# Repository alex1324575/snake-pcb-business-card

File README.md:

# Snake PCB Business Card

A USB-powered PCB business card with a 10 × 9 LED matrix, five buttons and Snake firmware. A passive NFC tag and a silkscreen QR code carry the contact URL.

**Firmware simulation.** The board and enlarged display show the same 90 PWM values from the C firmware: start, turn, collect four food pixels, hit a wall and display the score. See the [gameplay demo](docs/revc/GAMEPLAY_DEMO.md) for source, capture and reproduction details. This is a host simulation; hardware execution remains untested.

| Rev C — Top | Rev C — Bottom |
|---|---|
|  |  |

3D assembly previews use the current Rev C layout and all 125 fitted parts. The separate [rotation preview](docs/images/revc-3d-rotation.gif) shows assembly geometry with unlit LEDs. A [static isometric view](docs/images/revc-3d-isometric.png) and [model provenance](docs/revc/3D_VISUALIZATION.md) are also available. Public artwork uses **ALEX XU** and **https://example.com/**.

## Current revision

**Rev C is the current Altium prototype design.** CAD corrections, native validation and final CAM review are complete. Supplier process acceptance and first-article qualification remain open; all 14 physical tests are **NOT TESTED**.

| Check | Recorded result — 28 October 2026 |
|---|---|
| Native PCB DRC | 0 violations, 0 warnings, 0 waivers; all 43 stored rule records unchanged |
| Native schematic validation | 0 errors, 2 reviewed reset-bias warnings, retained without suppression |
| Saved-source audit | 135 schematic instances, 29 symbols, 15 footprints; 217 firmware contract checks passed |
| Manufacturing output review | Nine Gerbers and two plated-hole/slot NC files matched to the final saved PCB |
| Hardware qualification | P01–P14 NOT TESTED; no assembled-board result recorded |

The [verification guide](docs/VERIFICATION.md) identifies the reports, public-copy transformations and test limits. Layout compromises, including retained orthogonal NFC coil corners, are listed in [layout tradeoffs](docs/revc/LAYOUT_TRADEOFFS.md).

## Hardware

| Feature | Rev C implementation |
|---|---|
| Board | 85.6 × 54 mm, two layers, nominal 0.8 mm, four R2 corners |
| Finish | Black solder mask, white silkscreen, ENIG |
| MCU | STM32G030K8T6, Cortex-M0+, 64 KB Flash / 8 KB SRAM |
| Display | 90 red LEDs and IS31FL3737B PWM driver |
| Input | Four direction buttons and START |
| Power | USB-C 5 V, TPS7A2433DBVR 3.3 V regulator; no battery |
| Contact | Bottom QR artwork and ST25TN01K passive NFC tag |
| Programming | SWD test pads on both faces; TP7/SWCLK is on Top |

USB-C supplies power only. Firmware is programmed over SWD. NFC operates independently of USB power and is provisioned separately from the MCU.

## Open the design

Open [SnakeCard_RevC.PrjPcb](altium/SnakeCard_RevC.PrjPcb) in Altium Designer. The project contains the single-sheet schematic, routed PCB and local schematic/footprint libraries. The [Altium guide](docs/ALTIUM.md) describes the files and validation procedure.

| Purpose | Current Rev C files |
|---|---|
| Review the circuit | [Native schematic PDF](exports/SnakeCard_RevC_Schematic.pdf) and [hardware notes](docs/HARDWARE.md) |
| Review checks | [Verification](docs/VERIFICATION.md) and [final status record](verification/revc/FINAL_CHECK_STATUS.json) |
| Select parts | [Controlled BOM — SC-REVC-LCSC-P1](docs/revc/assembly/BOM.md) |
| Fabricate | [Gerber/NC files](fabrication/revc/) and [fabrication specification](docs/revc/FABRICATION_NOTES.md) |
| Assemble | [Assembly guide](docs/ASSEMBLY.md), [placement register](docs/revc/assembly/PLACEMENT_REGISTER.md) and [drawings](docs/revc/assembly/ASSEMBLY_REFERENCE.html) |
| Test the first board | [Bring-up](docs/BRINGUP.md) and [P01–P14 qualification record](docs/revc/electrical/QUALIFICATION_PLAN.md) |

The root KiCad project and earlier exports remain as the **historical KiCad revision**. They were not updated to Rev C. Do not combine their BOM, footprint, stencil, SWD or fabrication data with Rev C. See [revision history](docs/REVISION_HISTORY.md).

## Firmware

The C11 firmware uses register-level board support, with no heap or RTOS. It implements Snake, button debounce, PWM display control and fault recovery. Rev C retains the tested firmware source and release images; the original `RevB` binary filenames are retained. The native Rev C pin contract was checked separately. MCU execution remains untested.

From the repository root, with Python 3.9+ and an Arm GNU toolchain installed:

```sh
python firmware/tools/build.py --build
```

Host tests also require GCC, Clang or Microsoft C++ Build Tools:

```sh
python firmware/tools/build.py --test-host --sanitize
```

The [firmware guide](firmware/README.md) covers toolchains, checksums and controls. `firmware/tools/check_board_contract.py` checks the historical KiCad inputs; it does not replace the saved-native Rev C audit.

### Controls

- Press START to begin, pause or resume.
- Use the direction buttons to steer toward the flashing food pixel.
- Hold START for about 0.8 seconds to return to idle.
- Hold UP while idle to view the highest score from the current power session.
- Hold START during power-up to enter the LED/button diagnostic; release it and press START again to exit.

Assemble and measure one controlled first article before building additional cards. Use the [prototype plan](docs/PROTOTYPE_PLAN.md) to track supplier, assembly and qualification gates. Contribution and license information are in [CONTRIBUTING](CONTRIBUTING.md) and [THIRD_PARTY_NOTICES](THIRD_PARTY_NOTICES.md).

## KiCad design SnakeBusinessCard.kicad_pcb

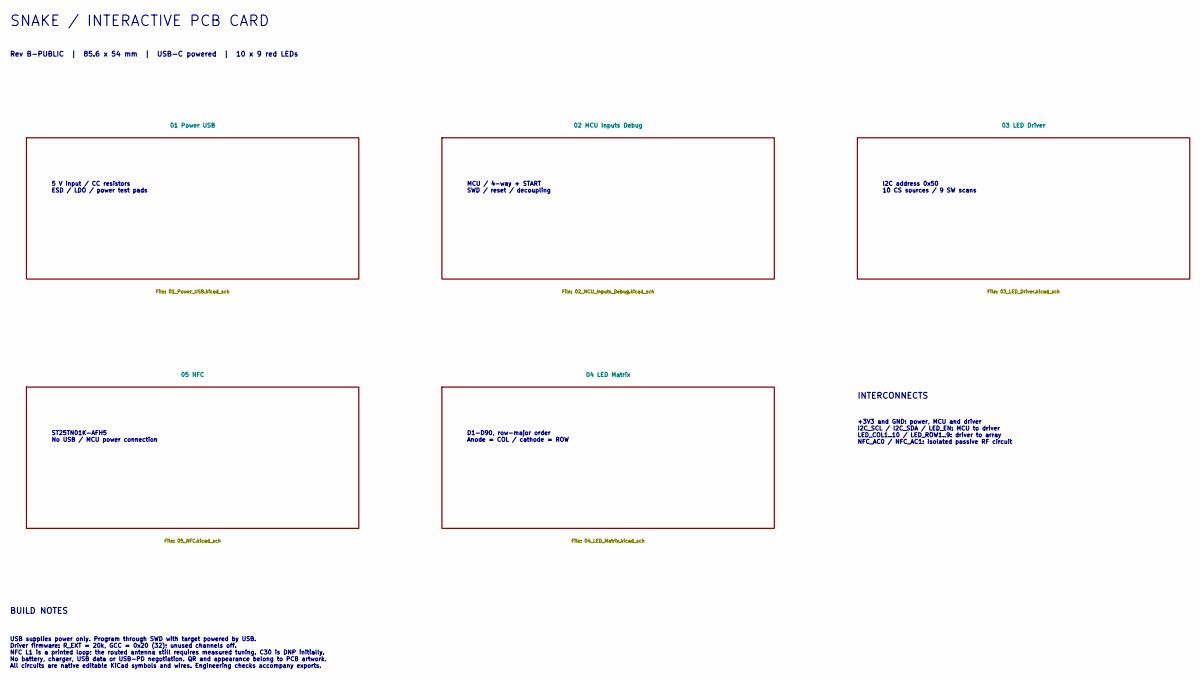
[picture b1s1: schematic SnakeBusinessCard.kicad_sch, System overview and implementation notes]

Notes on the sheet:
SNAKE / INTERACTIVE PCB CARD
Rev B-PUBLIC | 85.6 x 54 mm | USB-C powered | 10 x 9 red LEDs
5 V input / CC resistors ESD / LDO / power test pads
MCU / 4-way + START SWD / reset / decoupling
I2C address 0x50 10 CS sources / 9 SW scans
D1-D90, row-major order Anode = COL / cathode = ROW
ST25TN01K-AFH5 No USB / MCU power connection
INTERCONNECTS
+3V3 and GND: power, MCU and driver I2C_SCL / I2C_SDA / LED_EN: MCU to driver LED_COL1..10 / LED_ROW1..9: driver to array NFC_AC0 / NFC_AC1: isolated passive RF circuit
BUILD NOTES
USB supplies power only. Program through SWD with target powered by USB. Driver firmware: R_EXT = 20k, GCC = 0x20 (32); unused channels off. NFC L1 is a printed loop; the routed antenna still requires measured tuning. C30 is DNP initially. No battery, charger, USB data or USB-PD negotiation. QR and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

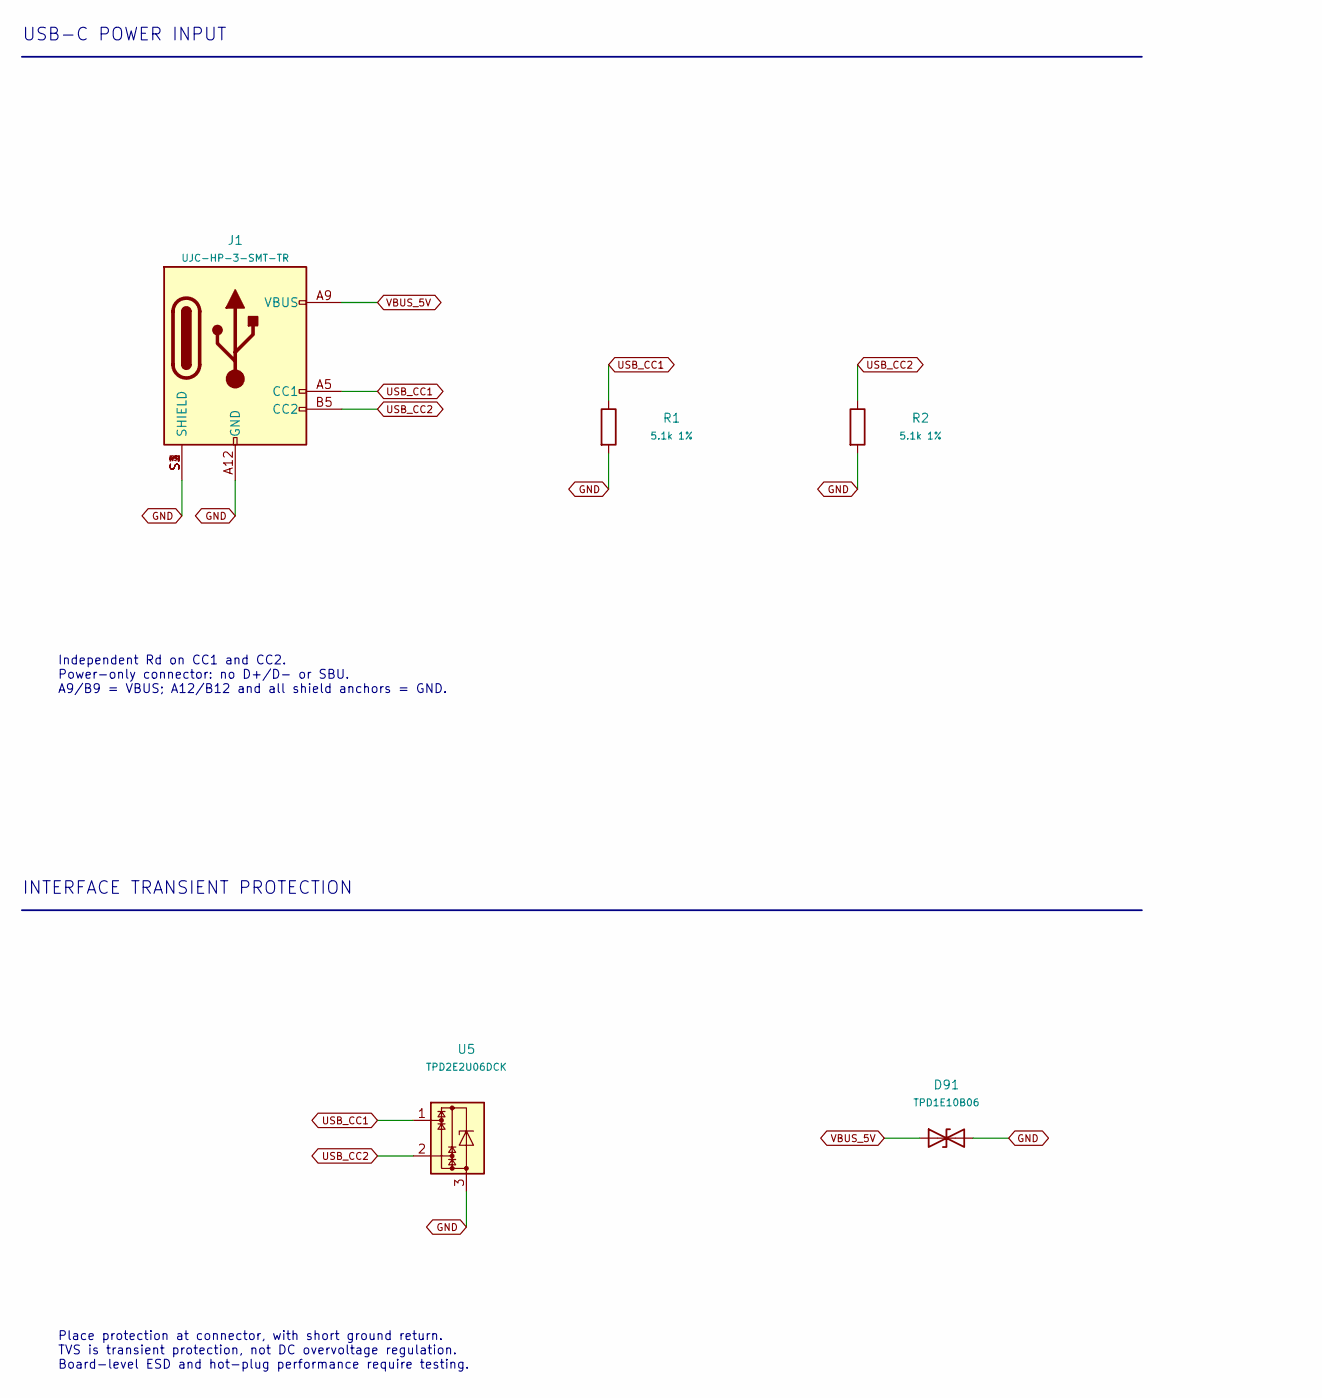
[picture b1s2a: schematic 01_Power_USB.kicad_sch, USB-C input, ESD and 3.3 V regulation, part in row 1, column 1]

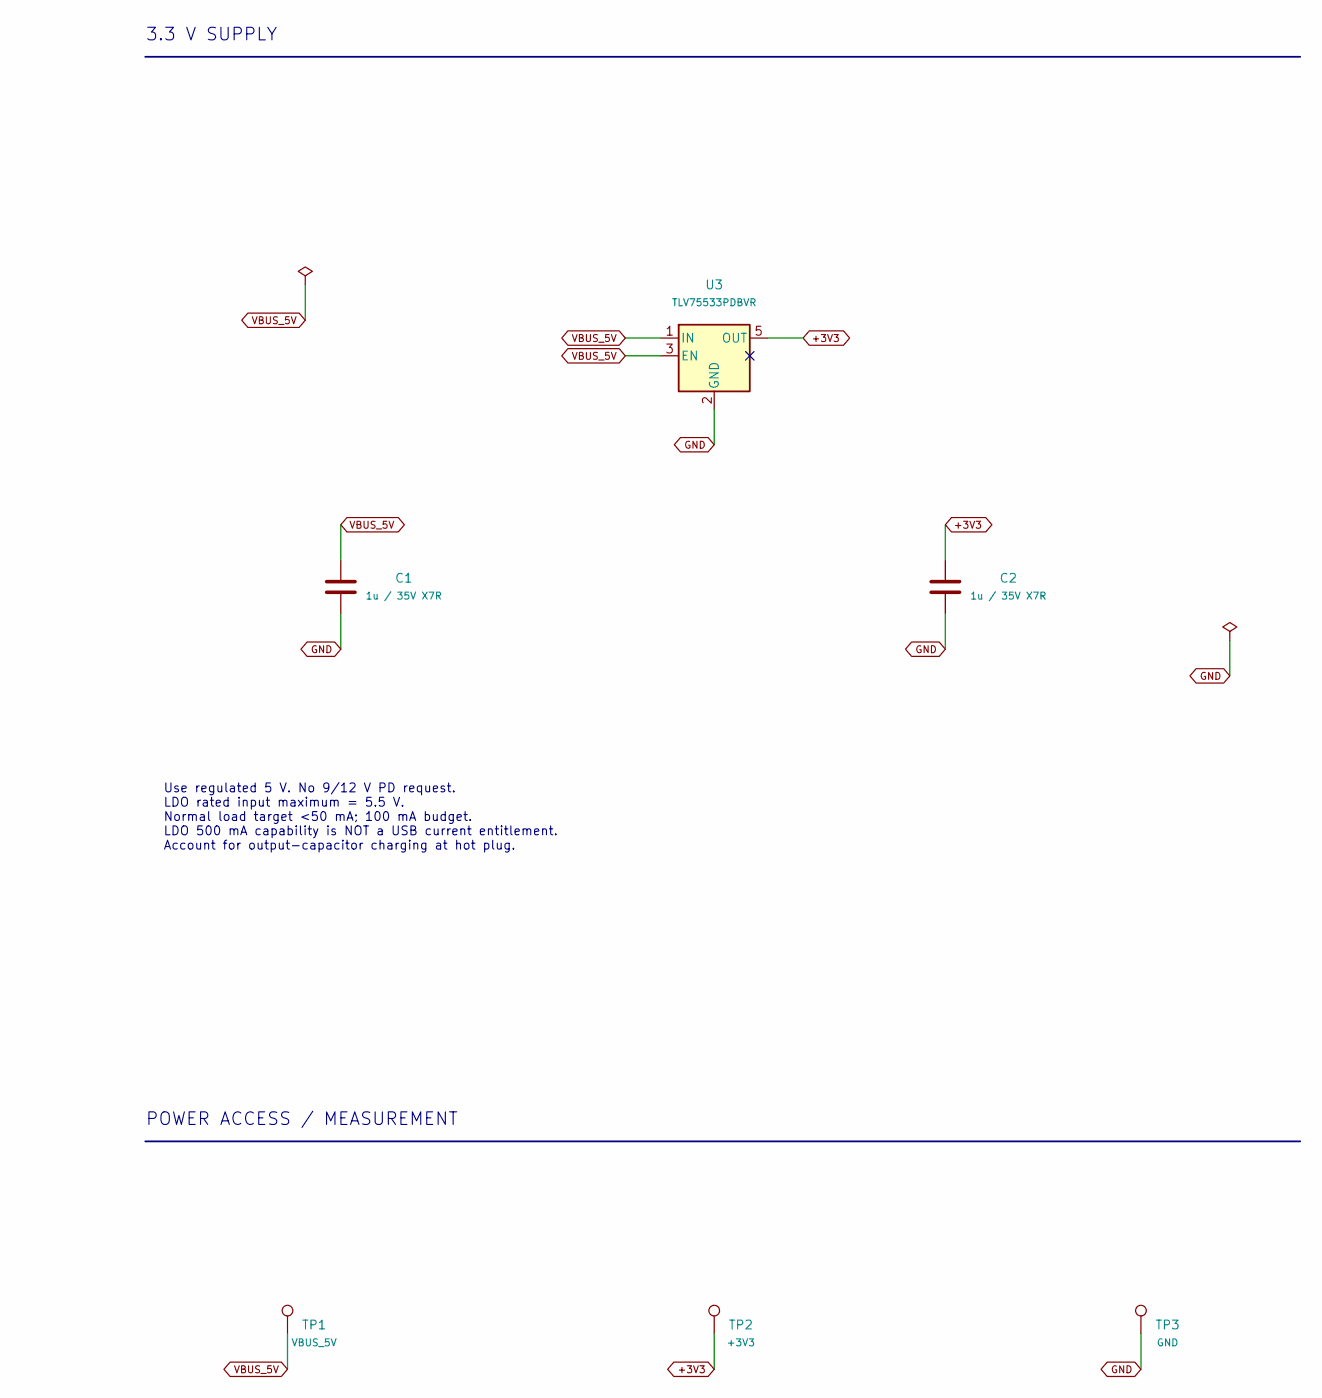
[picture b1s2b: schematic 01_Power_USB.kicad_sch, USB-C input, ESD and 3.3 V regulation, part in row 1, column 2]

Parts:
C1, C2: 1u / 35V X7R; C_0603_1608Metric; MPN C1608X7R1V105K080AC
D91: TPD1E10B06; D_SOD-523; MPN TPD1E10B06DYAR
J1: UJC-HP-3-SMT-TR; CUI_UJC-HP-3-SMT-TR; MPN UJC-HP-3-SMT-TR
R1, R2: 5.1k 1%; R_0603_1608Metric; MPN ERJ3EKF5101V
TP1: VBUS_5V; TestPoint_Pad_D1.0mm
TP2: +3V3; TestPoint_Pad_D1.0mm
TP3: GND; TestPoint_Pad_D1.0mm
U3: TLV75533PDBVR; SOT-23-5; MPN TLV75533PDBVR
U5: TPD2E2U06DCK; SOT-323_SC-70; MPN TPD2E2U06DCKR

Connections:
+3V3: C2.1, TP2.1, U3.5 (OUT); also elsewhere on the board
GND: C1.2, C2.2, D91.2 (A2), J1.A12 (GND), J1.B12 (GND), J1.S1 (SHIELD), J1.S2 (SHIELD), J1.S3 (SHIELD), J1.S4 (SHIELD), R1.2, R2.2, TP3.1, U3.2 (GND), U5.3; also elsewhere on the board
USB_CC1: J1.A5 (CC1), R1.1, U5.1
USB_CC2: J1.B5 (CC2), R2.1, U5.2
VBUS_5V: C1.1, D91.1 (A1), J1.A9 (VBUS), J1.B9 (VBUS), TP1.1, U3.1 (IN), U3.3 (EN)

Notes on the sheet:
USB-C POWER INPUT
Independent Rd on CC1 and CC2. Power-only connector: no D+/D- or SBU. A9/B9 = VBUS; A12/B12 and all shield anchors = GND.
INTERFACE TRANSIENT PROTECTION
Place protection at connector, with short ground return. TVS is transient protection, not DC overvoltage regulation. Board-level ESD and hot-plug performance require testing.
3.3 V SUPPLY
Use regulated 5 V. No 9/12 V PD request. LDO rated input maximum = 5.5 V. Normal load target <50 mA; 100 mA budget. LDO 500 mA capability is NOT a USB current entitlement. Account for output-capacitor charging at hot plug.
POWER ACCESS / MEASUREMENT

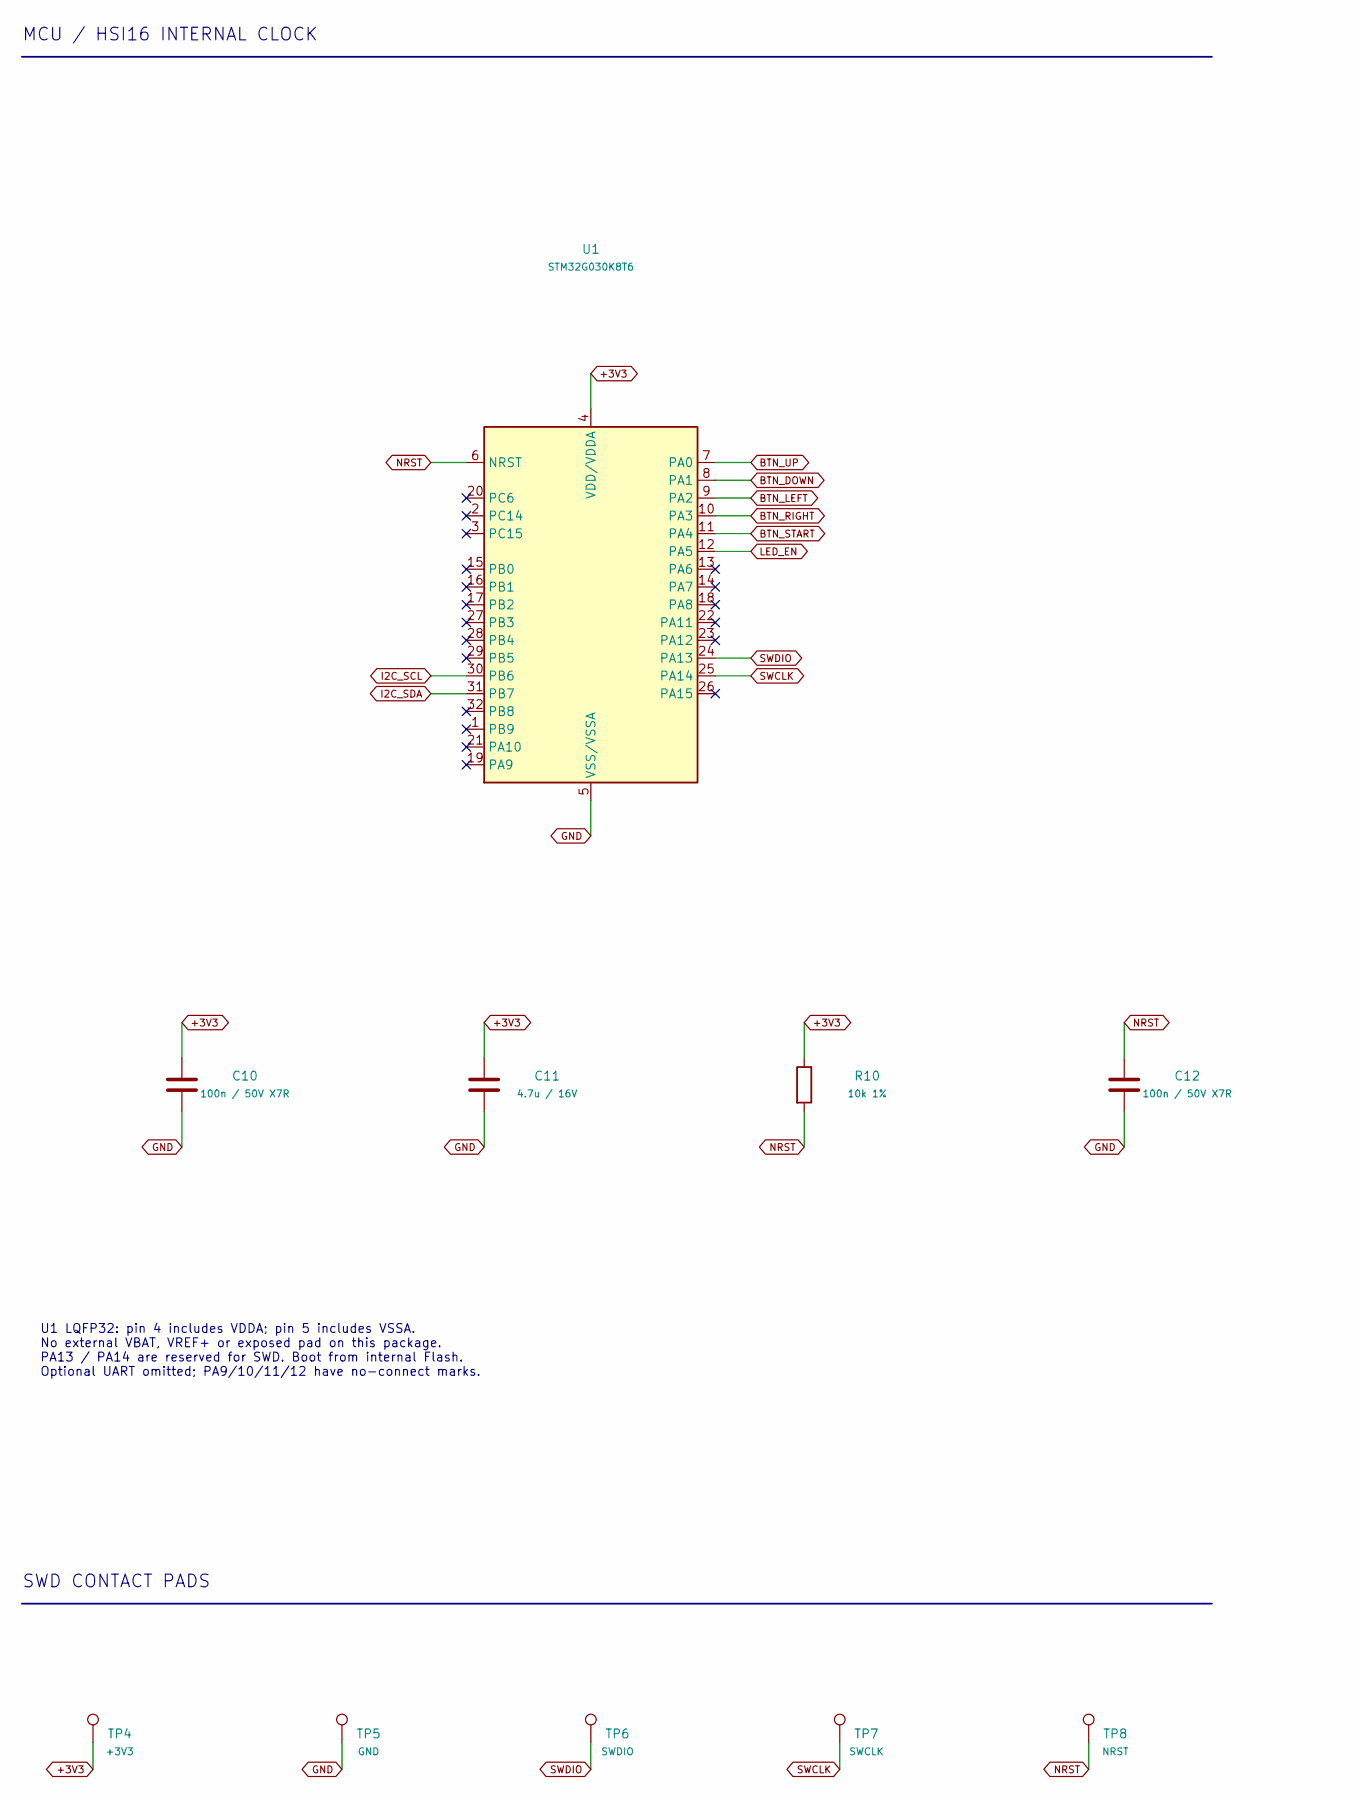
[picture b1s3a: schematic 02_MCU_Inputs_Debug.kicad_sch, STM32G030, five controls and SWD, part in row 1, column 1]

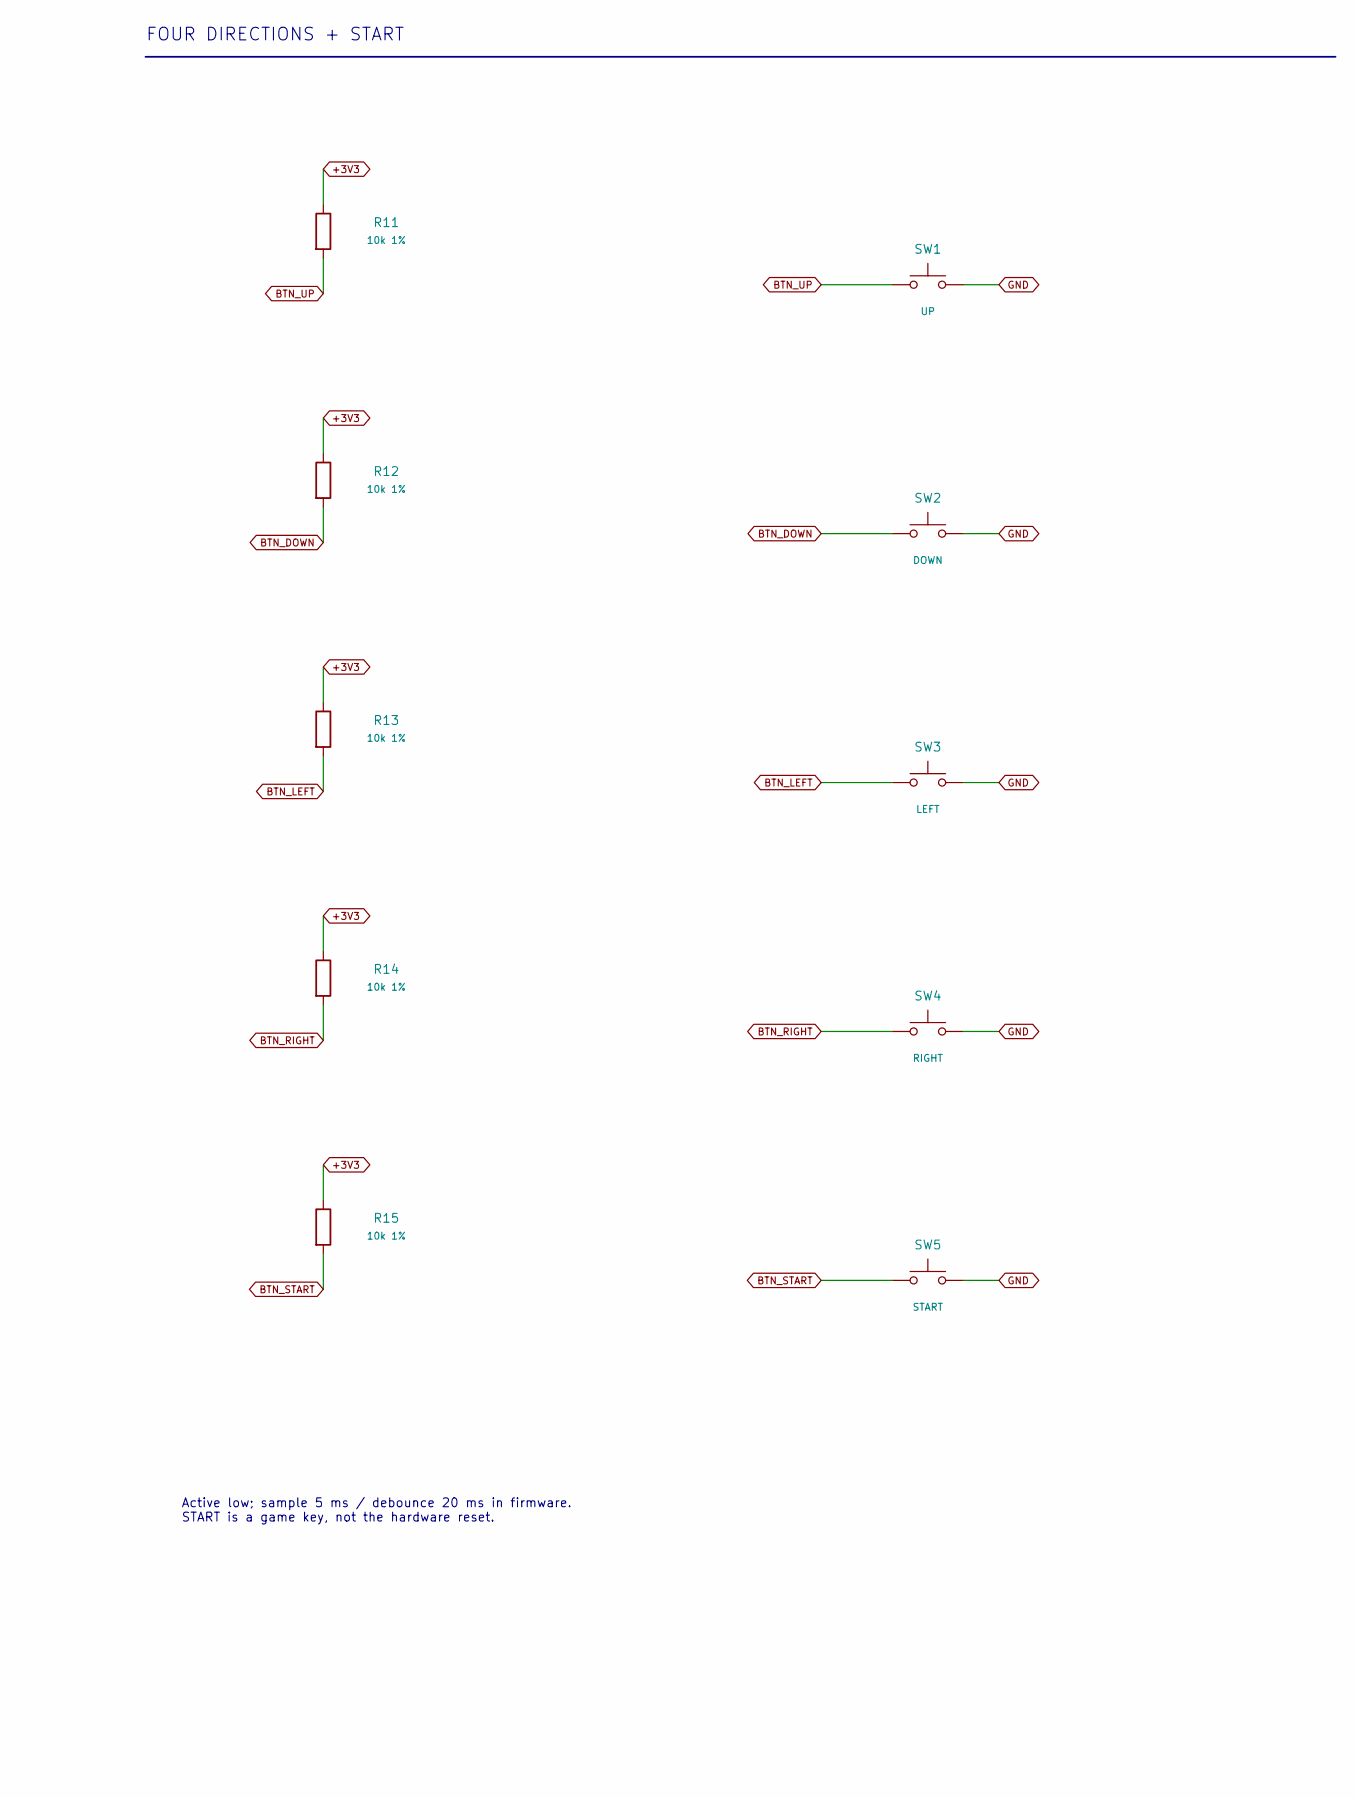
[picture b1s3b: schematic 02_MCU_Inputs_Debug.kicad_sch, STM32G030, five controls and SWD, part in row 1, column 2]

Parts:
C10, C12: 100n / 50V X7R; C_0603_1608Metric; MPN C1608X7R1H104K080AA
C11: 4.7u / 16V; C_0603_1608Metric; MPN GRM188Z71C475KE21D
R10, R11, R12, R13, R14, R15: 10k 1%; R_0603_1608Metric; MPN ERJ3EKF1002V
SW1: UP; SW_SPST_SKQG_WithStem; MPN SKQGABE010
SW2: DOWN; SW_SPST_SKQG_WithStem; MPN SKQGABE010
SW3: LEFT; SW_SPST_SKQG_WithStem; MPN SKQGABE010
SW4: RIGHT; SW_SPST_SKQG_WithStem; MPN SKQGABE010
SW5: START; SW_SPST_SKQG_WithStem; MPN SKQGABE010
TP4: +3V3; TestPoint_Pad_D1.0mm
TP5: GND; TestPoint_Pad_D1.0mm
TP6: SWDIO; TestPoint_Pad_D1.0mm
TP7: SWCLK; TestPoint_Pad_D1.0mm
TP8: NRST; TestPoint_Pad_D1.0mm
U1: STM32G030K8T6; LQFP-32_7x7mm_P0.8mm; MPN STM32G030K8T6

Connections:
+3V3: C10.1, C11.1, R10.1, R11.1, R12.1, R13.1, R14.1, R15.1, TP4.1, U1.4 (VDD/VDDA); also elsewhere on the board
BTN_DOWN: R12.2, SW2.1, U1.8 (PA1)
BTN_LEFT: R13.2, SW3.1, U1.9 (PA2)
BTN_RIGHT: R14.2, SW4.1, U1.10 (PA3)
BTN_START: R15.2, SW5.1, U1.11 (PA4)
BTN_UP: R11.2, SW1.1, U1.7 (PA0)
GND: C10.2, C11.2, C12.2, SW1.2, SW2.2, SW3.2, SW4.2, SW5.2, TP5.1, U1.5 (VSS/VSSA); also elsewhere on the board
I2C_SCL: U1.30 (PB6); also elsewhere on the board
I2C_SDA: U1.31 (PB7); also elsewhere on the board
LED_EN: U1.12 (PA5); also elsewhere on the board
NRST: C12.1, R10.2, TP8.1, U1.6 (NRST)
SWCLK: TP7.1, U1.25 (PA14)
SWDIO: TP6.1, U1.24 (PA13)

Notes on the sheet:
MCU / HSI16 INTERNAL CLOCK
U1 LQFP32: pin 4 includes VDDA; pin 5 includes VSSA. No external VBAT, VREF+ or exposed pad on this package. PA13 / PA14 are reserved for SWD. Boot from internal Flash. Optional UART omitted; PA9/10/11/12 have no-connect marks.
FOUR DIRECTIONS + START
Active low; sample 5 ms / debounce 20 ms in firmware. START is a game key, not the hardware reset.
SWD CONTACT PADS

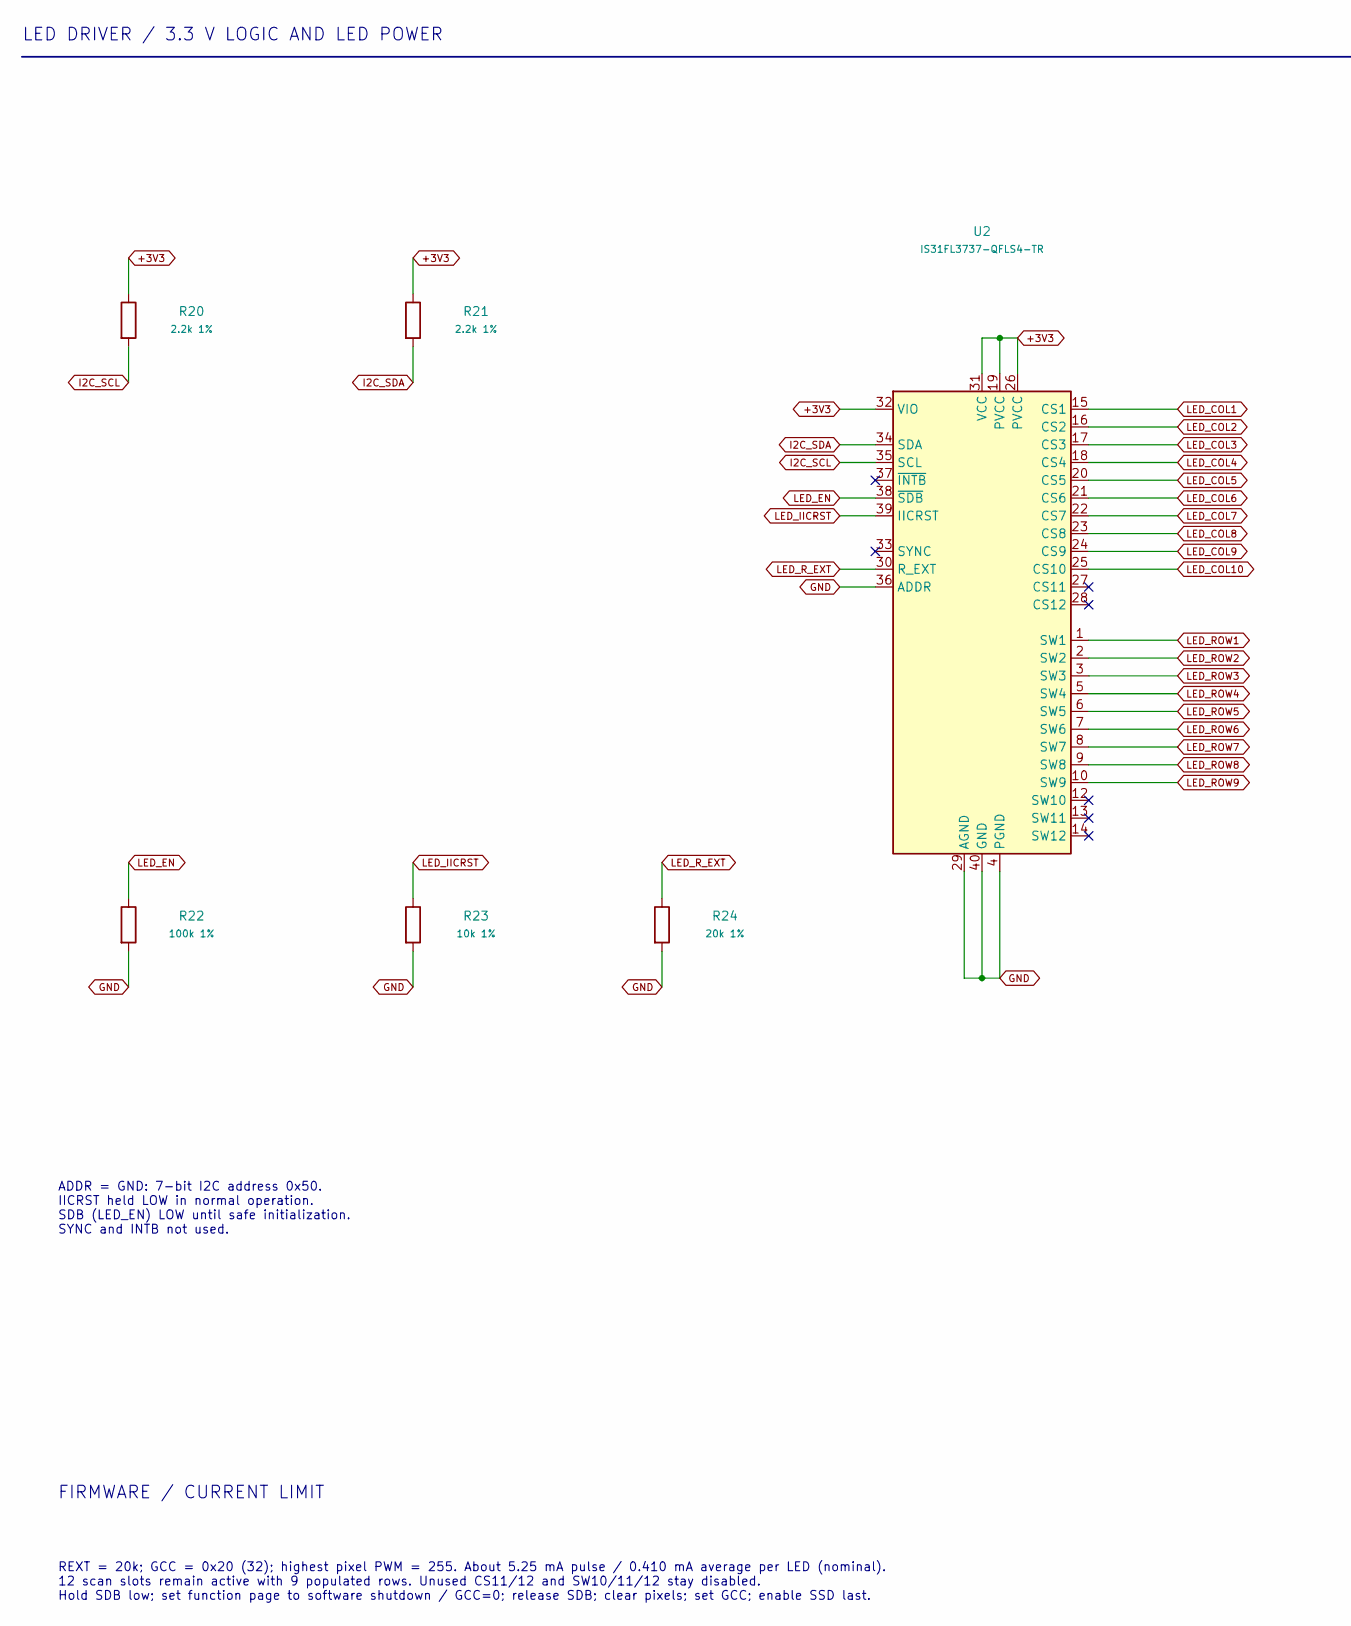
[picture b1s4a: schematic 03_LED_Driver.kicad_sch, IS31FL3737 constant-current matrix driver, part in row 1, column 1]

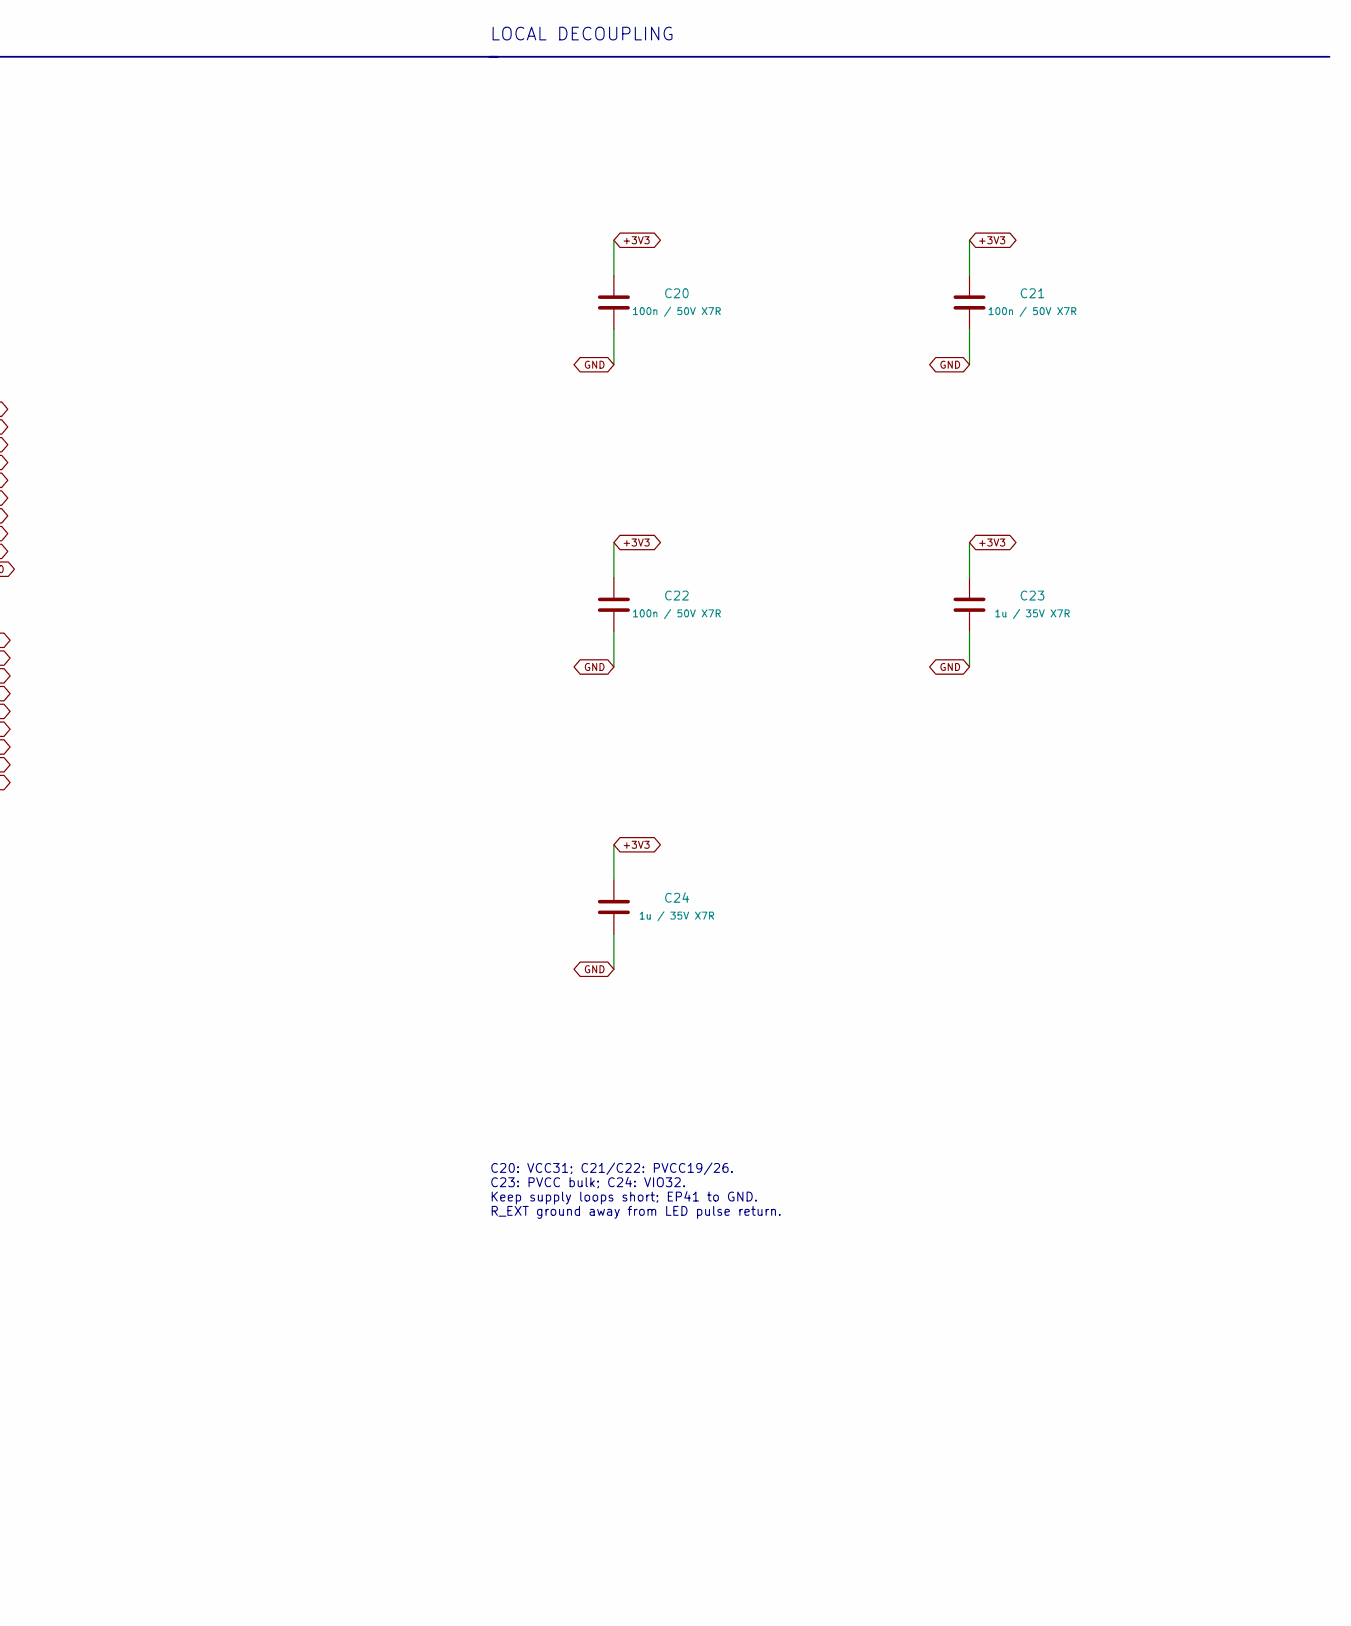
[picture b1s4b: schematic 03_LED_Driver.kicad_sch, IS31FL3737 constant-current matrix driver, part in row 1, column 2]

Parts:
C20, C21, C22: 100n / 50V X7R; C_0603_1608Metric; MPN C1608X7R1H104K080AA
C23, C24: 1u / 35V X7R; C_0603_1608Metric; MPN C1608X7R1V105K080AC
R20, R21: 2.2k 1%; R_0603_1608Metric; MPN ERJ3EKF2201V
R22: 100k 1%; R_0603_1608Metric; MPN ERJ3EKF1003V
R23: 10k 1%; R_0603_1608Metric; MPN ERJ3EKF1002V
R24: 20k 1%; R_0603_1608Metric; MPN ERJ3EKF2002V
U2: IS31FL3737-QFLS4-TR; IS31FL3737_QFN40_5x5mm_P0.4mm_EP3.4mm; MPN IS31FL3737-QFLS4-TR

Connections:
+3V3: C20.1, C21.1, C22.1, C23.1, C24.1, R20.1, R21.1, U2.19 (PVCC), U2.26 (PVCC), U2.31 (VCC), U2.32 (VIO); also elsewhere on the board
GND: C20.2, C21.2, C22.2, C23.2, C24.2, R22.2, R23.2, R24.2, U2.4 (PGND), U2.11 (PGND), U2.29 (AGND), U2.36 (ADDR), U2.40 (GND), U2.41 (GND); also elsewhere on the board
I2C_SCL: R20.2, U2.35 (SCL); also elsewhere on the board
I2C_SDA: R21.2, U2.34 (SDA); also elsewhere on the board
LED_COL1: U2.15 (CS1); also elsewhere on the board
LED_COL2: U2.16 (CS2); also elsewhere on the board
LED_COL3: U2.17 (CS3); also elsewhere on the board
LED_COL4: U2.18 (CS4); also elsewhere on the board
LED_COL5: U2.20 (CS5); also elsewhere on the board
LED_COL6: U2.21 (CS6); also elsewhere on the board
LED_COL7: U2.22 (CS7); also elsewhere on the board
LED_COL8: U2.23 (CS8); also elsewhere on the board
LED_COL9: U2.24 (CS9); also elsewhere on the board
LED_COL10: U2.25 (CS10); also elsewhere on the board
LED_EN: R22.1, U2.38 (~SDB); also elsewhere on the board
LED_IICRST: R23.1, U2.39 (IICRST)
LED_ROW1: U2.1 (SW1); also elsewhere on the board
LED_ROW2: U2.2 (SW2); also elsewhere on the board
LED_ROW3: U2.3 (SW3); also elsewhere on the board
LED_ROW4: U2.5 (SW4); also elsewhere on the board
LED_ROW5: U2.6 (SW5); also elsewhere on the board
LED_ROW6: U2.7 (SW6); also elsewhere on the board
LED_ROW7: U2.8 (SW7); also elsewhere on the board
LED_ROW8: U2.9 (SW8); also elsewhere on the board
LED_ROW9: U2.10 (SW9); also elsewhere on the board
LED_R_EXT: R24.1, U2.30 (R_EXT)

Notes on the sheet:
LED DRIVER / 3.3 V LOGIC AND LED POWER
ADDR = GND: 7-bit I2C address 0x50. IICRST held LOW in normal operation. SDB (LED_EN) LOW until safe initialization. SYNC and INTB not used.
LOCAL DECOUPLING
C20: VCC31; C21/C22: PVCC19/26. C23: PVCC bulk; C24: VIO32. Keep supply loops short; EP41 to GND. R_EXT ground away from LED pulse return.
FIRMWARE / CURRENT LIMIT
REXT = 20k; GCC = 0x20 (32); highest pixel PWM = 255. About 5.25 mA pulse / 0.410 mA average per LED (nominal). 12 scan slots remain active with 9 populated rows. Unused CS11/12 and SW10/11/12 stay disabled. Hold SDB low; set function page to software shutdown / GCC=0; release SDB; clear pixels; se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
